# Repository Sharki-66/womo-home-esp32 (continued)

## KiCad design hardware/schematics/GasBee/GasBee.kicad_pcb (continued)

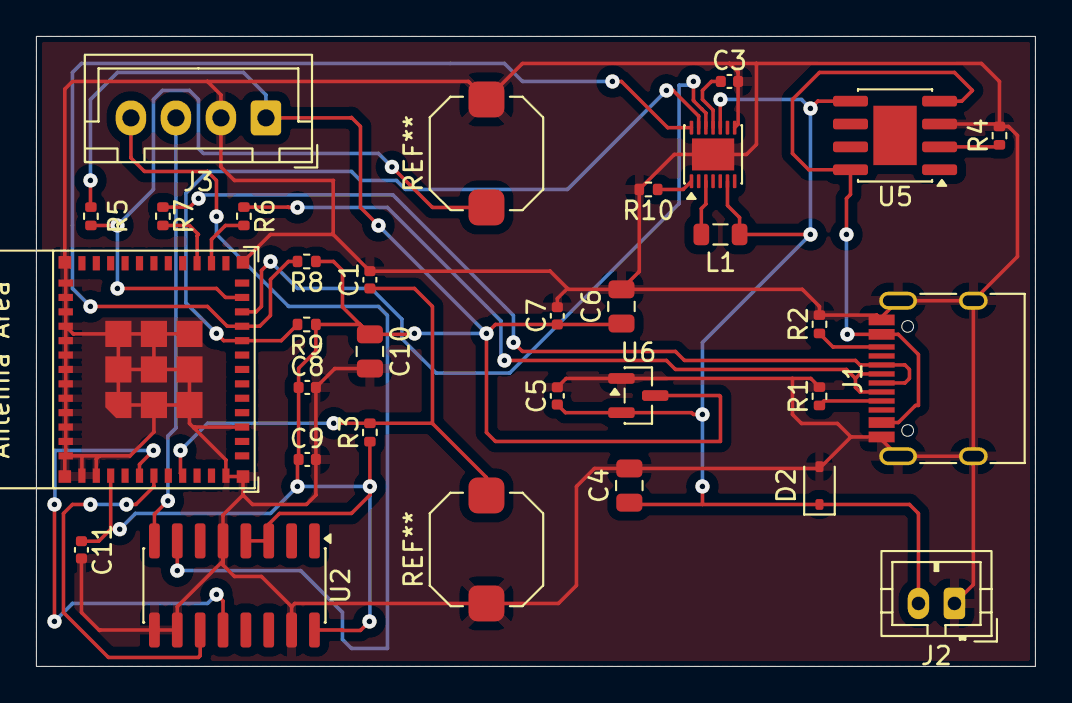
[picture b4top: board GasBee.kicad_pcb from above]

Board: 2 copper layers, 55.5 x 35.0 mm, 32 parts (0 on the bottom side), 23 nets.

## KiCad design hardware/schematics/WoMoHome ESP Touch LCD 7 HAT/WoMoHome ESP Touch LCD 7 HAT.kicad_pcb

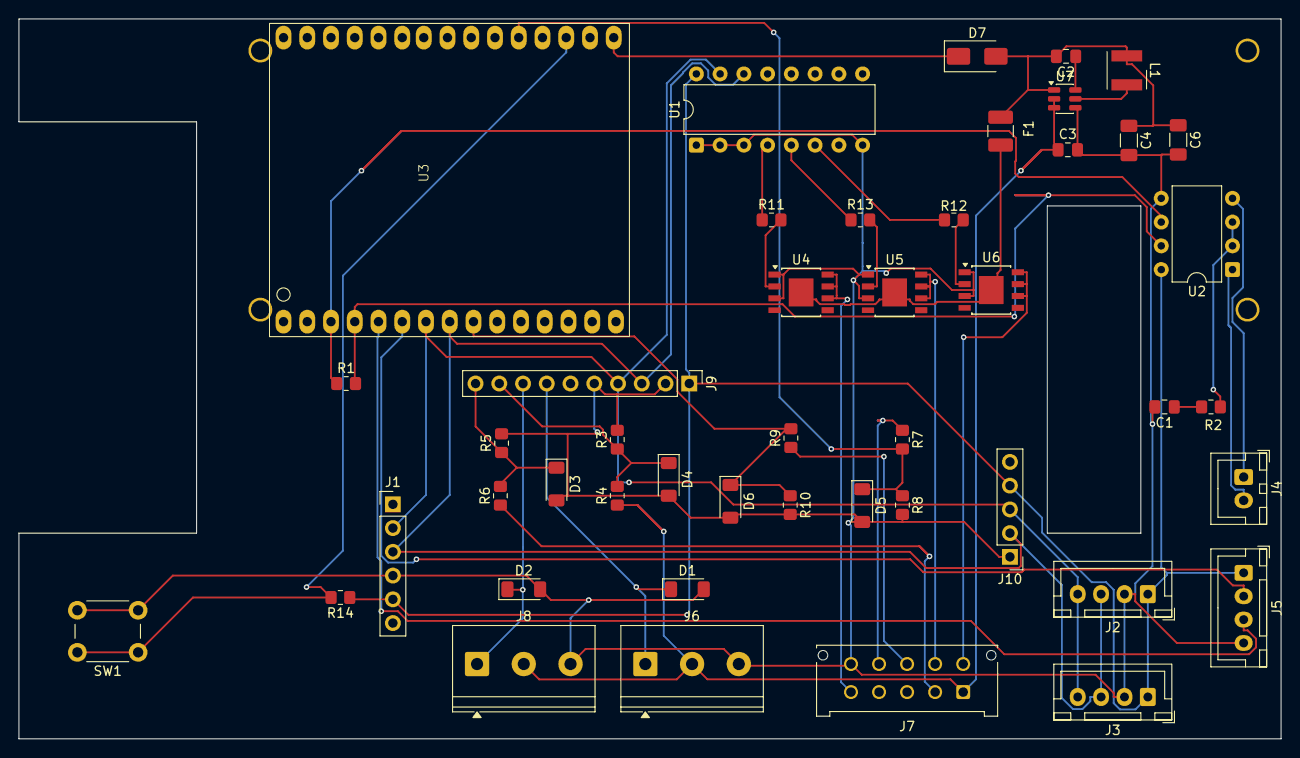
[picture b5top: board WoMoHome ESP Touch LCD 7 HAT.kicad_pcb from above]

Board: 2 copper layers, 135.0 x 77.0 mm, 46 parts (0 on the bottom side), 37 nets.

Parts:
C1, C3: 10 nF; C_0805_2012Metric_Pad1.18x1.45mm_HandSolder
C2: 100nF; C_0805_2012Metric_Pad1.18x1.45mm_HandSolder
C4, C6: 22µF; C_1206_3216Metric_Pad1.33x1.80mm_HandSolder
D1, D2, D3, D4, D5, D6: BZV55B3V3; D_MiniMELF
D7: SS34; D_SMA
F1: 12V 2A; Fuse_1210_3225Metric_Pad1.42x2.65mm_HandSolder
J1: BNO055 IMU; PinHeader_1x06_P2.54mm_Vertical
J2: BME680 #1 Außen; JST_XH_B4B-XH-A_1x04_P2.50mm_Vertical
J3: BME680 #0 Innen; JST_XH_B4B-XH-A_1x04_P2.50mm_Vertical
J4: RS485; JST_XH_B2B-XH-A_1x02_P2.50mm_Vertical
J5: HX711 GasWaage; JST_XH_B4B-XH-A_1x04_P2.50mm_Vertical
J6: Sensor Grauwasser; TerminalBlock_Phoenix_PT-1,5-3-5.0-H_1x03_P5.00mm_Horizontal
J7: LT452 Malibu; Molex_Micro-Fit_3.0_43045-1012_2x05_P3.00mm_Vertical
J8: Sensor Frischwasser; TerminalBlock_Phoenix_PT-1,5-3-5.0-H_1x03_P5.00mm_Horizontal
J9: ADS1115_Module (ADC); PinHeader_1x10_P2.54mm_Vertical
J10: PCF8523 RTC; PinHeader_1x05_P2.54mm_Vertical
L1: 3.9 µH; L_Wurth_WE-LQSH-4020
R1, R11, R12, R13: 1k; R_0805_2012Metric_Pad1.20x1.40mm_HandSolder
R2, R14: 10k; R_0805_2012Metric_Pad1.20x1.40mm_HandSolder
R3, R5, R8, R10: 22k; R_0805_2012Metric_Pad1.20x1.40mm_HandSolder
R4, R6, R7, R9: 100k; R_0805_2012Metric_Pad1.20x1.40mm_HandSolder
SW1: Reset; SW_PUSH_6mm
U1: PCF8574AP; DIP-16_W7.62mm
U2: SP3485CP; DIP-8_W7.62mm
U3: SIM7600 ESP32; SIM7600X-ESP32
U4, U5, U6: BTS40K2-1EJC; Infineon_PG-DSO-8-43
U7: AP63203WU; TSOT-23-6

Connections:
+3.3V: J1.5, J2.1, J3.1, J5.1, J9.1, J10.4, R14.1, U1.16 (VDD), U2.8 (VCC)
/5 V: C2.2, C4.1, C6.1, D7.2 (A), F1.1, L1.1, U7.1 (FB)
/5 V Fuse: F1.2, U4.9 (VS), U5.9 (VS), U6.9 (VS)
/12 V - AUS: J7.6, U6.6 (OUT), U6.7 (OUT), U6.8 (OUT)
/12 V - EIN: J7.7, U5.6 (OUT), U5.7 (OUT), U5.8 (OUT)
/12V-Kontrolle: J7.8, R9.1
/Multimedia: J7.5, U4.6 (OUT), U4.7 (OUT), U4.8 (OUT)
/Netz: J7.9, R7.1
/SB: J7.2, R6.1
/SCL: J1.3, J2.3, J3.3, J9.3, J10.2, U1.14 (SCL), U3.8 (IO27)
/SDA: J1.2, J2.4, J3.4, J9.4, J10.3, U1.15 (SDA), U3.7 (IO26)
/SFW: D2.1 (K), J8.1, J9.8
/SGW: D1.1 (K), J6.1, J9.7
/WB +: C3.1, J6.2, J7.1, J8.2, R4.1, U7.2 (EN), U7.3 (IN)
GND: C1.2, C3.2, C4.2, C6.2, D1.2 (A), D2.2 (A), D3.2 (A), D4.2 (A), D5.2 (A), D6.2 (A), J1.4, J2.2, J3.2, J5.4, J6.3, J7.10, J8.3, J9.2, J9.5, J10.1, R3.2, R5.2, R8.2, R10.2, SW1.2, U1.1 (A0), U1.2 (A1), U1.3 (A2), U1.8 (GND), U2.5 (GND), U4.1 (GND), U4.3 (DEN), U5.1 (GND), U5.3 (DEN), U6.1 (GND), U6.3 (DEN), U7.4 (GND)
unnamed: C1.1, R2.2
unnamed: D3.1 (K), J9.10, R5.1, R6.2
unnamed: D4.1 (K), J9.9, R3.1, R4.2
unnamed: D5.1 (K), R7.2, R8.1, U3.20 (S_VN/39)
unnamed: D6.1 (K), R9.2, R10.1, U3.9 (IO4)
unnamed: D7.1 (K), U3.16 (VBUS)
unnamed: J4.1, U2.4 (DI)
unnamed: J4.2, U2.1 (RO)
unnamed: J5.2, U3.6 (IO25)
unnamed: J5.3, U3.5 (IO34)
unnamed: R11.1, U1.4 (P0)
unnamed: R13.1, U1.5 (P1)
unnamed: R12.2, U1.6 (P2)
unnamed: R1.1, U2.6 (A), U3.3 (IO32)
unnamed: R1.2, U2.7 (B), U3.4 (IO33)
unnamed: R2.1, U2.2 (~RE), U2.3 (DE)
unnamed: R14.2, SW1.1, U3.18 (RST/EN)
unnamed: R11.2, U4.2 (IN)
unnamed: R13.2, U5.2 (IN)
unnamed: R12.1, U6.2 (IN)
unnamed: C2.1, U7.6 (BST)
unnamed: L1.2, U7.5 (SW)

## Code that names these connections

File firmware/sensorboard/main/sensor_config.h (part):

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 *                  3.3 V power supply |    P |  🟩 |  3V3 | 1          E         1 | GND  | 🟩  | G     | Ground
 *                  3.3 V power supply |    P |  🟩 |  3V3 | 2          S         2 | TX   | 🟩  | I/O/T | U0TXD, GPIO43, CLK_OUT1
 *                               Reset |    I |  🟩 |  RST | 3          P         3 | RX   | 🟩  | I/O/T | U0RXD, GPIO44, CLK_OUT2
 *    (ADC1_CH3, RTC, GPIO4) Batt1 KFZ | I/O/T|  🟨 |    4 | 4          3         4 | 1    | 🟨  | I/O/T | Tank1 Frisch (GPIO1, RTC, ADC1_CH0)
 *  (ADC1_CH4, RTC, GPIO5) Batt2 Board | I/O/T|  🟨 |    5 | 5          2         5 | 2    | 🟨  | I/O/T | Tank2 Grau (GPIO2, RTC, ADC1_CH1)
 *         DC1_CH5, RTC, GPIO6) WAKEUP | I/O/T|  🟨 |    6 | 6          -         6 | 42   | 🟩  | I/O/T | MTMS, GPIO42
 *   (ADC1_CH6, RTC, GPIO7) Display 5V | I/O/T|  🟨 |    7 | 7          S         7 | 41   | 🟩  | I/O/T | MTDI, GPIO41
 *     (ADC2_CH4, RTC, GPIO15) I2C SCL | I/O/T|  🟨 |   15 | 8          3         8 | 40   | 🟩  | I/O/T | MTDO, GPIO40
 *     (ADC2_CH5, RTC, GPIO16) I2C SDA | I/O/T|  🟨 |   16 | 9          -         9 | 39   | 🟩  | I/O/T | MTCK, GPIO39
 *(ADC2_CH6, U1TXD, RTC, GPIO17) Licht | I/O/T|  🟨 |   17 | 10         W        10 | 38   | 🟨  | I/O/T | RGB_LED  (GPIO38)
 *(ADC2_CH7, U1RXD, RTC, GPIO18) Pumpe | I/O/T|  🟨 |   18 | 11         R        11 | 37   | 🟥  | I/O/T | ⚠ PSRAM (GPIO37, nicht nutzbar!)
 *               (ADC1_CH7, RTC) GPIO8 | I/O/T|  ⬜ |    8 | 12         O        12 | 36   | 🟥  | I/O/T | ⚠ PSRAM (GPIO36, nicht nutzbar!)
 *                ADC1_CH2, RTC, GPIO3 | I/O/T|  ⬜ |    3 | 13         O        13 | 35   | 🟥  | I/O/T | ⚠ PSRAM (GPIO35, nicht nutzbar!)
 *                   GPIO46, STRAP/LOG | I/O/T|  🟩 |   46 | 14         M        14 | 0    | 🟩  | I/O/T | BOOT/STRAP, GPIO0
 *          GPIO9 Tank alt Grau (Rev6) | I/O/T|  🟨 |    9 | 15         -        15 | 45   | 🟨  | I/O/T | HX711 SCK (GPIO45)
 *       GPIO10 Tank alt Frisch (Rev6) | I/O/T|  🟨 |   10 | 16         1        16 | 48   | 🟩  | I/O/T | Onboard WS2812 RGB-LED (GPIO48)
 *          GPIO11 12V EIN (Rev6: AUS) | I/O/T|  🟨 |   11 | 17                  17 | 47   | 🟨  | I/O/T | HX711 DOUT (GPIO47)
 *          GPIO12 12V AUS (Rev6: EIN) | I/O/T|  🟨 |   12 | 18                  18 | 21   | 🟨  | I/O/T | AC 220V Sence (GPIO21, RTC)
 *  (ADC2_CH2, RTC, GPIO13) Multimedia | I/O/T|  🟨 |   13 | 19                  19 | 20   | 🟩  | I/O/T | USB_D+, GPIO20, RTC
 *   (ADC2_CH3, RTC, GPIO14) 12V Sence | I/O/T|  🟨 |   14 | 20                  20 | 19   | 🟩  | I/O/T | USB_D-, GPIO19, RTC
 *                    5 V power supply |    P |  🟩 |   5V | 21                  21 | GND  | 🟩  | G     | Ground
 *                              Ground |    G |  🟩 |  GND | 22                  22 | GND  | 🟩  | G     | Ground
 * ------------------------------------|------|-----|------|------------------------|------|------|-----|-------|-----------------------------------------
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#endif

// ====================================================================================
// I2C-Bus für Sensoren auf Header J1 (SDA=GPIO16, SCL=GPIO15)
// ====================================================================================
#define SENSOR_I2C_EXT_PORT 0
#define SENSOR_I2C_EXT_SDA_GPIO 16
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#define SENSOR_HX711_SCALE_B -0.15674f

// ====================================================================================
// ESP-NOW Transport (Display Link) – vormals RS485 GPIO9/10/8
// GPIO8 (ehemaliger RS485-DE) wird im Deep-Sleep LOW gehalten (floating prevention).
// ====================================================================================
#define SENSOR_ESPNOW_DE_LEGACY_GPIO  8   /* Ehemaliger RS485-DE: im Deep-Sleep LOW halten */

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// ====================================================================================
// Analog ADC (Battery & Tank Sensors)
// ====================================================================================
#define SENSOR_BATT1_ADC_CHANNEL 3     // GPIO4 (Batt1 Kfz)
#define SENSOR_BATT2_ADC_CHANNEL 4     // GPIO5 (Batt2 Board)
#define SENSOR_TANK1_ADC_CHANNEL 0     // GPIO1 (Frischwasser)
#define SENSOR_TANK2_ADC_CHANNEL 1     // GPIO2 (Grauwasser)

// Batterie-Kalibrierung (U_kalibriert = U_gemessen * SCALE + OFFSET_mV)
// Pipeline: ADC-mV × (122/22) = U_roh → × SCALE + OFFSET = U_kalibriert
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
// Tank-Kalibrierung (U_kalibriert = U_gemessen * SCALE + OFFSET_mV)
// Hinweis Rev 5: 0-1V Sensoren liegen direkt am ADC (kein Spannungsteiler).
// Ab Rev 6 (J9 Frischwasser → GPIO1, J10 Grauwasser → GPIO2), je Kanal:
//   J9/J10 Pin 1 = +12V (Sensorversorgung), Pin 2 = Signal, Pin 3 = GND
//   Signal ─ R32/R33 100k nach GND, ─ R30/R34 4k7 in Reihe ─ ADC-Pin,
//   am ADC-Pin D1/D2 BZV55B3V3 (Z-Diode 3,3V) nach GND als Überspannungsschutz.
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// Die Schalter schließen kumulativ (bei 75% sind 25%+50%+75% alle geschlossen).
//
// Lösung ab Rev 6: 1 ADC-Pin pro Tank über ein Widerstandsnetzwerk
// (Pin-Konflikt mit GPIO17/18 damit erledigt – neue Pins GPIO9/10).
//
// Schaltung Rev 6 (aus Schaltplan, Molex Micro-Fit J2/J3, Pin 5 = GND):
//   Frischwasser J2 ("Wassertank LT45x")  → GPIO10 (ADC1_CH9)
//     3.3V ─ R5 10k ─┬─ R6 10k ─ GPIO10
//                    ├─ R7  1k  ─ J2.1
//                    ├─ R8  2k2 ─ J2.2
//                    ├─ R9  4k7 ─ J2.3
//                    └─ R10 10k ─ J2.4         (J2.6 nicht belegt)
//   Grauwasser J3 ("Abwassertank LT45x")  → GPIO9 (ADC1_CH8)
//     3.3V ─ R28 10k ─┬─ R25 10k ─ GPIO9
//                     ├─ R23 1k  ─ J3.1
//                     ├─ R22 2k2 ─ J3.2
//                     ├─ R21 4k7 ─ J3.3
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// Implementierung (noch ausstehend, erst ab SENSOR_BOARD_REV 6):
//   - analog_sensor.c: Pegelerkennung anhand ADC-Spannungsschwellen
//   - sensor_config.h: ADC-Kanäle (ADC1_CH9/CH8) + Schwellwerte hier eintragen
//   - Offen: Vorrang, wenn neue (GPIO1/2) und alte Tanksensoren angeschlossen sind
// ====================================================================================

// ====================================================================================
// Board Power / Multimedia GPIOs (LBE-Steuerung über bistabiles Relais)
// ====================================================================================
#define SENSOR_RGB_LED_GPIO 48             // Onboard WS2812 RGB-LED (GPIO48, bestätigt)
// 12V EIN/AUS wurden im Schaltplan getauscht (Stand 25c2ed2, 2026-10-20 → Rev 0.6):
//   Rev 5: GPIO11 → Q1 → "12V - EIN",  GPIO12 → Q2 → "12V - AUS"
//   Rev 6: GPIO11 → R41 → Q6 (IRLML6244) → J5.1 "12V - AUS"
//          GPIO12 → R42 → Q7 (IRLML6244) → J5.2 "12V - EIN"
#if SENSOR_BOARD_REV >= 6
#define SENSOR_PWR_12V_ON_GPIO 12      // Schaltausgang: LBE EIN (Relais-Puls)
#define SENSOR_PWR_12V_OFF_GPIO 11     // Schaltausgang: LBE AUS (Relais-Puls)
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#endif
#define SENSOR_PWR_12V_SENSE_GPIO 14   // Eingang: LBE Spannungsfeedback
#define SENSOR_AC_SENSE_GPIO 21        // Eingang: 230V Netzkontrolle
#define SENSOR_MULTIMEDIA_PWR_GPIO 13  // Schaltausgang: Multimedia Power

// Pulslänge für das bistabile LBE-Relais (EIN/AUS). Gilt für Boot-EIN-Puls
// (app_main.c), Laufzeit-Puls (espnow_modem.c) und Deep-Sleep-AUS-Puls
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// bestätigen und ggf. reduzieren.
#define SENSOR_PWR_12V_PULSE_MS 500

// 12V-Sense (GPIO14): echte Rückmeldung des Bordnetz-Relais.
// 1 = ctrl-Topic-Feld `pwr_on` meldet den an GPIO14 GEMESSENEN Zustand (Display-
//     Button zeigt Realität statt nur des kommandierten Zustands).
// 0 = reines Soft-Flag (nur der zuletzt kommandierte Zustand).
#define SENSOR_PWR_12V_SENSE_ENABLE      1
// Aktiver Pegel des Sense-Eingangs. Annahme analog AC-Sense: 12V vorhanden -> HIGH.
// TODO(hardware): per Messung an GPIO14 verifizieren; bei invertierter Beschaltung 0.
#define SENSOR_PWR_12V_SENSE_ACTIVE_HIGH 1
// Nach einem Relais-Puls braucht die 12V-Schiene Zeit zum Auf-/Abbau. Solange wird
// weiter der kommandierte Zustand gemeldet, nicht der Sense-Pin.
#define SENSOR_PWR_12V_SENSE_GRACE_MS    2500
// GPIO13-Defekt (2026-08-30) geklärt: echter Hardware-Schaden durch Verpolung
// an Steckverbinder J7 ("LT452 Malibu", 10-pol. Molex Micro-Fit) – Multimedia-
// Leitung lag dabei auf GND, ESP32-Ausgang wurde bei HIGH hart kurzgeschlossen
// (Ausgangstreiber vermutlich durchlegiert). Kein Software-Fix möglich.
// Ebenfalls betroffen: GPIO17/Licht (lag auf vertauschtem 12V-Kontroll-Signal).
// GPIO18/Pumpe unbeschädigt trotz gleichem Vorfall.
// Entscheidung: Kein Pin-Remapping auf dieser Platine – neue Platinenrevision
// wird bestellt (korrekter J7, RS485-Transceiver entfernt, Q5 richtig gepolt).
// Diese Config gilt für die NEUE Platine mit unbeschädigten GPIOs 13/17/18.
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// Schaltprinzip Rev 6 (gilt auch für Multimedia):
//   GPIO → 4k7 → 2N7002 (Gate-Pulldown 100k) → zieht Gate des P-Kanal
//   IRLML2244 (Pull-up 100k an +12V) → schaltet +12V auf J5
//   Multimedia: GPIO13 → R37 → Q3 → Q8 → J5.10
//   GPIO18 → R35 → Q4 → Q9  → J5.9 = Licht  (Schaltplan-Netz "/Pumpe")
//   GPIO17 → R36 → Q5 → Q10 → J5.8 = Pumpe  (Schaltplan-Netz "/Licht")
// Schaltplan Rev 0.6 hat Licht/Pumpe an J5 vertauscht. Laut Datenblatt LT 45x
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
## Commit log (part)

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2025-10-26 Create .gitignore with ESP-IDF ignore rules
2025-10-26 Update hardware components in README_Version2.md
    Removed PCF8575 GPIO Expander and updated power supply details.
2025-10-26 Update display resolution in README
2025-10-28 Initial ESP-IDF project import
2025-11-01 Add comprehensive community open hardware platforms documentation
2025-11-20 Snapshot 2025-11-20
2025-12-07 snapshot: 2025-12-07
2025-12-14 Fix LTE control function scoping for GPS module
2025-12-15 Snapshot 2025-12-15 – Version 1.0
    TODO: kleinere Fehler; Farbe Ducato grau; Verbrauchsanzeige; zweiter BME680; Sleepmode
2025-12-20 chore: address review feedback
2026-02-12 refactor: Demo-ZIP entpackt (3275 Files) und esp-iot-solution aus Git entfernt
    - docs/software/ESP32-S3-Touch-LCD-7-Demo/ (entpackt) entfernt – ZIP reicht als Referenz
    - docs/software/ESP32-S3-Touch-LCD-7-Demo.zip entfernt (lokal vorhanden)
    - esp-iot-solution/ aus Index entfernt (externes Repo, separat klonen)
    - Veraltete Architektur-Doku entfernt
2026-02-12 refactor: Bilder, Docs, PDFs konsolidieren + Docs mit Cross-References
    Bilder:
    - firmware/display/docs/images/weather-icons/ entfernt (Duplikat von sdcard/)
    - docs/images/Ducato.jpg entfernt (Duplikat)
    - Ducato-Designdateien → sdcard/images/ducato/
    - images/weather-icons/ (1008 Dateien) → sdcard/images/weather-icons-all/
    Dokumentation:
2026-02-12 tools: Strukturprüfung + Git pre-commit Hook
    - tools/check-structure.sh: Prüft Verzeichnisse, Pflichtdateien,
    fehlplatzierte Ordner, große Dateien, Doku-Querverweise
    - .githooks/pre-commit: Ruft check-structure.sh bei jedem Commit auf
    - git config core.hooksPath .githooks aktiviert den Hook
2026-02-13 feat(sensorboard): WiFi STA + HTTP-Server für Parkhilfe (Horizont)
    - sensor_wifi: WiFi STA verbindet sich mit RUTX11 AP 'Malibu-622'
    - NVS-gespeicherte Credentials (Fallback auf sensor_config.h Defaults)
    - mDNS: womo-sensor.local
    - Auto-Reconnect mit Retry-Pause
    - sensor_http: HTTP-Server auf Port 80
    - /api/imu → JSON (yaw, roll, pitch, cal, calibrated)
2026-02-13 feat(display+sensor): WiFi Passwort-Austausch über RS485
    Display empfängt wifi_pass_request vom Sensor und antwortet mit
    den aktuell verbundenen WiFi-Credentials (SSID + Passwort aus NVS).
    Display-Seite:
    - womo_rs485_display.c: Handler für type=wifi_pass_request in
    parse_json_packet – liest aktuelle SSID, holt Passwort aus
    Known-List, sendet wifi_config Command zurück
2026-02-17 Sensorboard: 5-Level Luftdruck-Trend implementiert
    - Pressure-Trend mit 5 Zuständen: falling_fast/falling/steady/rising/rising_fast
    - 24h-Historie (96 Samples à 15min), 3h-Fenster für Trend-Berechnung
    - Schwellwerte: ±0,5 hPa/3h und ±2,5 hPa/3h
    - NVS-Persistenz alle 10 Samples (2,5h)
2026-02-17 Sensorboard: Kleinere Verbesserungen und Cleanup
    - app_main.c, sensor_http.c, womo_rs485.c: Diverse Anpassungen
    - horizon.html: Web-Interface Update
2026-02-17 Hardware: TJA1051.pdf entfernt (nicht mehr benötigt)
2026-02-18 feat: Meteoalarm-Integration mit GPS-Badge und Popup
    - womo_meteoalarm.{c,h}: Neues Modul für Meteoalarm-API
    - HTTP-Fetch für coordinates/{lat}/{lon}
    - CAP-JSON-Parsing: Severity, Headline, Region, Expires
    - Hintergrundtask mit 30-Min-Intervall (5-Min-Retry)
    - 60 s earliest_fetch nach Systemstart (TLS-Kollisionsvermeidung)
    - NTP-Sync-Gate: Fetch erst nach gültiger Systemzeit
2026-02-19 Display: TLS-Fix, Geocode Nominatim, HTTP-Mutex
    TLS-Verbindungen (Wetter, Geocode, Meteoalarm) schlugen fehl wegen
    zu wenig internem SRAM (~39 KB frei, mbedTLS braucht ~50 KB).
    Fixes:
    - MBEDTLS_EXTERNAL_MEM_ALLOC=y: mbedTLS nutzt jetzt PSRAM (4.8 MB frei)
    - ISRG Root X1 PEM direkt eingebettet statt crt_bundle_attach für
    Wetter + Geocode (spart RAM, reicht für Let's Encrypt)
2026-02-19 README: Projektbeschreibung ohne technische Details
    Beschreibt das WoMo-Home-System aus Nutzersicht:
    - Motivation und Problemstellung
    - Überwachte Betriebsdaten (Energie, Gas, Wasser, Klima, Navigation)
    - Systemaufbau (Sensorboard, Display, Router)
    - Warum Eigenbau (Genauigkeit, Prognosen, Open Source)
    Technische Details bleiben in den Unter-READMEs und docs/.
2026-02-19 Docs: Veraltete Dokumentation entfernt, Index aktualisiert
    Entfernt (beziehen sich auf altes 3-Board-Setup mit Walter Modem):
    - MODEM_BOARD.md, CONNECTION_MATRIX.md, software-architecture.md
    - docs_hardware_overview/components/wiring_Version2.md
    - hardware-notes.md (Platzhalter), .gitignore, Amazon-Bild
    Behalten: 4× Waveshare Display-Specs (aktuell)
    docs/README.md: Neuer Index mit Links zu Hardware-Specs und Firmware-READMEs
2026-02-20 Fix: BSEC NVS Einheiten-Bug, Intervall 30 min; Spec ctrl-Topic bereinigt; Walter→Sensorboard
    - bme680_sensor.c: now_ns/1000 korrekt als now_us verwenden (war ns vs µs Vergleich
    → speicherte alle ~3 s statt alle 10 min → IAQ-Sprung nach Reboot)
    - BSEC_STATE_SAVE_INTERVAL: 10 min → 30 min
    - copilot-instructions.md: ctrl-Topic wifi_target/wifi_active/lte_target/lte_active
    entfernt (Sensorboard kennt Router-Zustand nicht; Display pollt Router direkt)
    - bat-Topic: soc? entfernt (nicht implementiert, nur Rohspannung)
2026-02-21 Fix: GasBee – Kalibrierung + Diagnose HX711
    - gasbee_config.h: Kalibrierung mit echten Messwerten (21.02.2026)
    offset=-278300, scale=0.00003999 (18 kg / 450090 LSB)
    DOUT=GPIO4, SCK=GPIO5 (GPIO2 war Strapping-Pin)
    - app_main.c: Pull-Up auf DOUT aktiviert (floating-Schutz)
    - app_main.c: Diagnose raw=0 + Min/Max pro Messzyklus im Log
2026-02-21 feat: Threshold-Settings, Locale-Fix, Sunset-Textfarben, Ducato-Bug
    - Settings-Modal: Grenzwerte Gas/Frisch/Grau mit +/-5%-Buttons, NVS-Persistenz
    - Locale: Threshold-Abschnitt DE/EN lokalisiert (5 neue STR_THRESH_*-IDs)
    - Modals: lv_obj_del_async() -> kein 1s-Schliess-Haenger mehr
    - Theme: Ducato bleibt grau bei temp. Zeitfehler (kein DAY-Reset)
    - Theme: Textfarben bei SUNSET/SUNRISE/NIGHT korrekt weiss (theme_mode_is_daylike)
2026-02-23 Docs: Fotos Display (vorne) und Sensorboard (hinten) in README eingebaut
2026-02-23 Display: Skalenstriche (25/50/75%) in Tank-Widget hinzugefügt
2026-02-26 todo Wetter, Vibe Coding, verbesserungen
2026-03-01 sensorboard: GPIO-Pinbelegung korrigiert (12V EIN=GPIO11, 12V AUS=GPIO12, Multimedia=GPIO13)
2026-03-06 feat(display): Router-LED-Modal, WiFi-Watchdog, Konnektivitäts-Button, Sonnenstand
    - womo_router_leds_modal: Neues Modal mit RUTX11 LED-Status (Power/WiFi/Signal/SIM)
    - womo_wifi: WiFi-Watchdog mit unbegrenztem Reconnect-Versuch
    - main: Router-LED-Button im Konnektivitäts-Modal Header integriert
    - womo_router_uci: AP-Banderkennung (2.4/5 GHz via iwinfo channel/hwmode)
    - womo_sun_calc: Sonnenauf-/-untergangsberechnung für Theme-Steuerung
    - copilot-instructions: LVGL v8->v9 Migrationsanalyse (betroffene Dateien)
2026-03-06 hw(sensorboard): KiCad Schaltplan aktualisiert, Gerber + Fertigungsdaten Rev 1.0
    - Sensorboard KiCad-Dateien aktualisiert (PCB, Schaltplan, Projekt)
    - Autosave-/Lock-Dateien entfernt
    - Gerber-Dateien für alle Layer hinzugefügt
    - Fertigungspaket Rev 1.0 (BOM, Bestückung, Positionen, IPC-Netlist)
    - Interactive BOM (ibom.html) hinzugefügt
2026-03-07 feat(display): Boot-Optimierungen, Theme-Fix, WeatherCache, WiFi-Async
    - WiFi async connect: parallel zu Display-HW+UI, spart ~1.5s
    - Bootzeit <4s (vorher 6-7s): -O2, Bootloader WARN, 150ms delay
    - Weather icon: lv_image_cache_drop() fix (stale LVGL cache bug)
    - Weather/Meteoalarm: Reconnect nach WiFi-Trennung korrekt
    - SUNRISE theme: weißer Ducato + schwarze Texte (war grau)
    - Perf-Monitor: 2 Zeilen FPS+CPU (ohne ms-Timing)
2026-03-08 feat(display): Locale-Vollständigkeit, Fenster-Stacking-Fix, UI-Feintuning
    - Locale (DE/EN): Tank Frisch/Grau, Gas Vorne/Hinten, Einstellungen,
    Kfz, Schliessen + Sofortaktualisierung bei Sprachwechsel
    - Settings-Modal: Titel + Close-Button sofort lokalisiert (s_title_lbl,
    s_close_lbl als statische Pointer in settings_locale_cb)
    - Fenster-Stacking: Konnektivitäts-Close schließt Router-LEDs-Modal mit
    (womo_router_leds_modal_close() in destroy_modal)
2026-03-08 feat(sensorboard): Protokoll- und Sensor-Updates
2026-03-11 feat(power): Schlafstrom reduzieren + zentrale Log-Konfiguration
    - BNO055 in Suspend-Modus vor Deep Sleep (OPR_MODE=CONFIG, PWR_MODE=SUSPEND)
    - HX711 Power-Down vor Deep Sleep (SCK HIGH >60µs)
    - RS485 DE-Pin (GPIO8) auf LOW einfrieren (gpio_hold_en) vor Sleep, freigeben nach Wake
    - sensor_log_init(): alle Log-Tags zentral in sensor_config.h konfigurierbar
    - sdkconfig.defaults: Touch-Wakeup-Konfiguration ergänzt
    Schlafstrom: 19 mA → 7 mA (restliche 5 mA: USB-UART-Bridge auf DevKit)
2026-03-17 fix(sensor): RS485, BLE, RTC – div. Korrekturen
2026-03-21 router-webui: GPS, Clients-CGI, Cron/Cache-System
    - poll.sh: GPS via gpsctl (-i/-x/-a/-v/-p/-s), Fix aus Status
    - cgi-bin/clients: iwinfo assoclist → JSON (Busybox-awk kompatibel)
    - cgi-bin/poll: stdout von poll.sh nach /dev/null (HTTP-Header-Fix)
    - HTML: GPS-Karte (Fix, Position, Höhe, Speed, Sats)
    - HTML: 4-spaltig auto-fit Grid (AP/WLAN/LTE/GPS)
    - HTML: refreshApClients() via CGI statt ubus file/exec
2026-03-23 display: UI-Layout überarbeitet und Schaltflächen verbessert
    - Backlight-Button: schwarzer Diagonalstrich (2px) als Aus-Schalter-Symbol
    - Backlight-/CPU-Fenster: LOG_LEVEL-Guard für RS485-Label und Perf-Toggle
    - Status-Label: Pill-Form, hellgrau opaque, Textfarbe immer schwarz
    - Settings-Button: hellgrauer Hintergrund, 90° gedreht, neben WiFi-Button
    - WiFi/LTE-Icons: je 2px zur Mitte versetzt
    - IMU- und Innenluft-Block getauscht, neu positioniert
2026-03-29 hardware(kicad): Sensorboard Rev 1.0 – Schematic/PCB aktualisiert, Produktionsdateien aus Tracking entfernt
2026-03-29 assets: SD-Card Logos/Icons hinzugefügt; Copilot Instructions aktualisiert
2026-03-30 Display Review: Zeitanzeige-Bug, toten Code entfernen, Dokumentation bereinigen
    Agent-Logs-Url: https://github.com/Sharki-66/womo-home-esp32/sessions/8188c8e4-4277-449b-82d5-038c526c6d8a
2026-04-05 Website: Display-Screenshots, UI-Verbesserungen, README aktualisiert
    - website/ komplett neu hinzugefügt (Astro 5 + Tailwind CSS v4)
    - 14 Display-Screenshots (screen1-17.jpg) eingebunden
    - Hero: 2 Einzelbilder + Collage-Kachel mit Hover-Galerie
    - Anfragen-Button entfernt, Nav aufgeräumt
    - Features: Klima, WLAN-Management, Horizont beschreibungen angepasst
    - Hardware-Liste: RTC ergänzt
2026-04-07 Update README.md
    Hinweis auf LT 45x
2026-04-07 Fix image file extension from .jpg to .png
2026-04-13 Prüfpunkt aus VS Code für Cloud-Agent-Sitzung
2026-04-13 fix: tinfo-Initialisierung in womo_display_http.c sichern
    Agent-Logs-Url: https://github.com/Sharki-66/womo-home-esp32/sessions/5917bc73-a8a2-4ada-9461-fd47006cb57e
2026-04-14 feat(sensorboard): Web-Dashboard mit vollständiger Steuerung
    - sensor_wifi: sensor_wifi_get_ap_info() für SSID + RSSI (esp_wifi_sta_get_ap_info)
    - rs485_modem: rs485_modem_execute_cmd_json(cJSON*) für parametrisierte Befehle
    - sensor_http: GET /api/status (WiFi connected/SSID/IP/RSSI)
    - sensor_http: POST /api/cmd nutzt rs485_modem_execute_cmd_json
    - dashboard.html: vollständiges Web-UI (800x480)
    - Status-Pill mit Alarm-Level (grün/orange/rot), Fehler-Acknowledge

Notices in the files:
firmware/sensorboard/main/sensor_config.h:
SPDX-FileCopyrightText: 2025-2026 Hajo Harms
SPDX-License-Identifier: MIT
